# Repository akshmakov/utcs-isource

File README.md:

# utcs-isource

Current Source Module (Schematic and PCB) for micro Transcranial Current Stimulalation (**utCS**)

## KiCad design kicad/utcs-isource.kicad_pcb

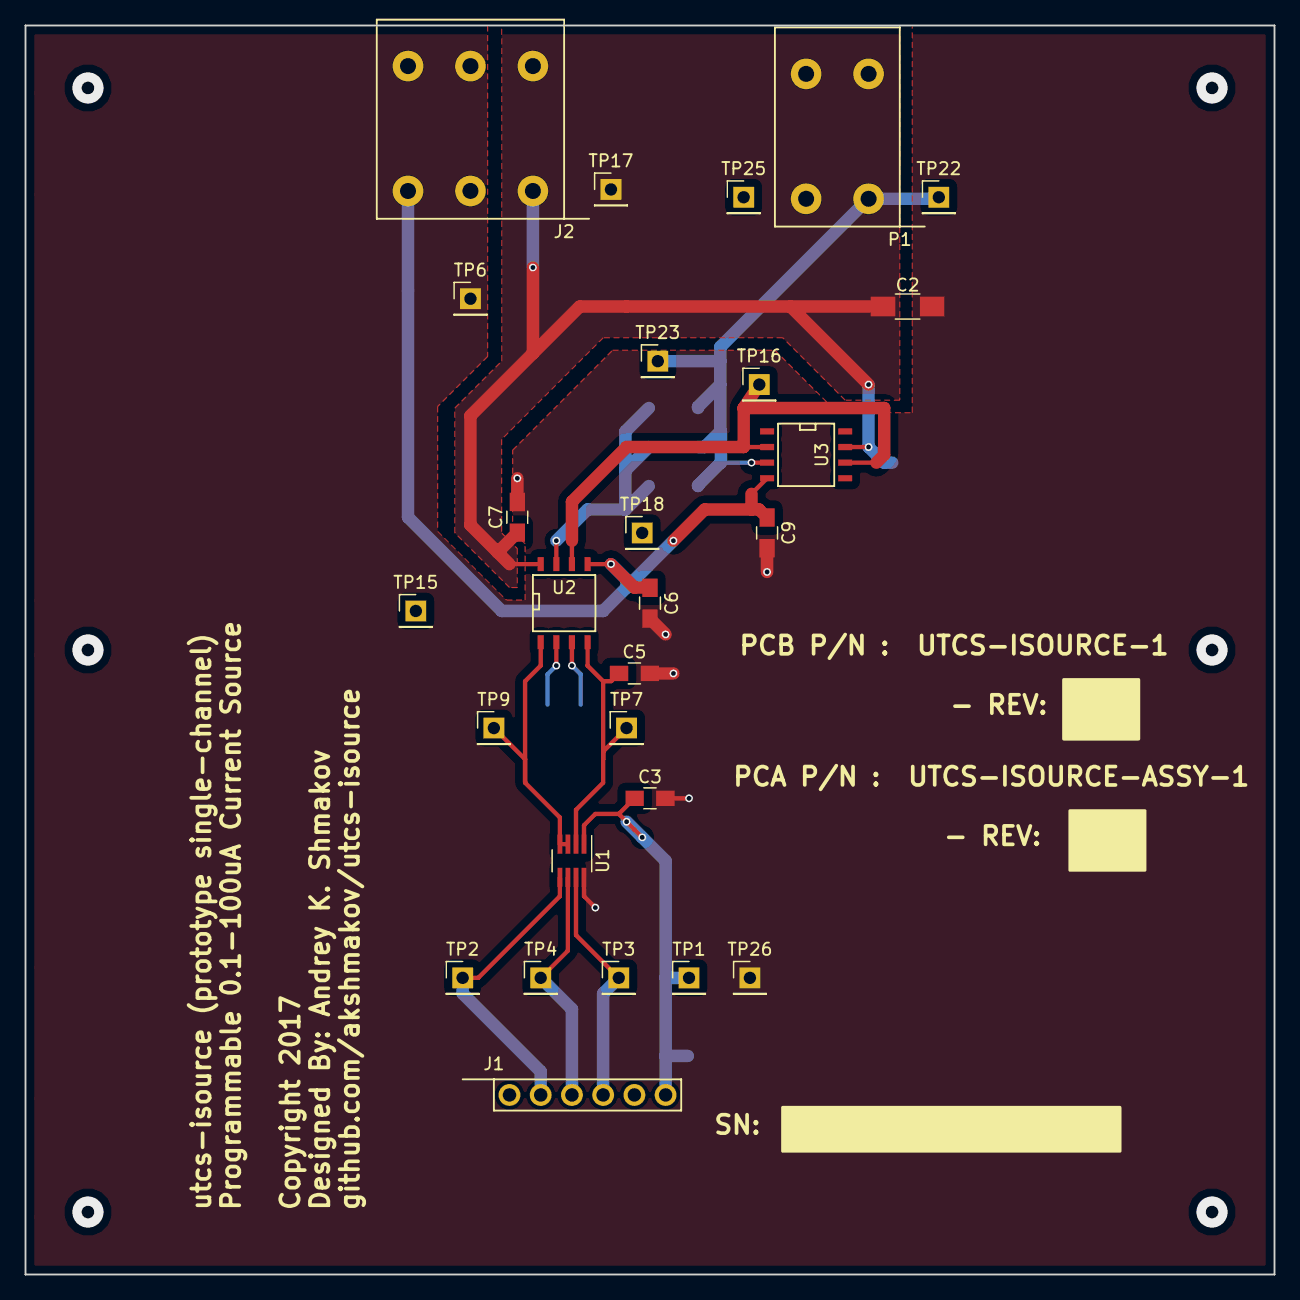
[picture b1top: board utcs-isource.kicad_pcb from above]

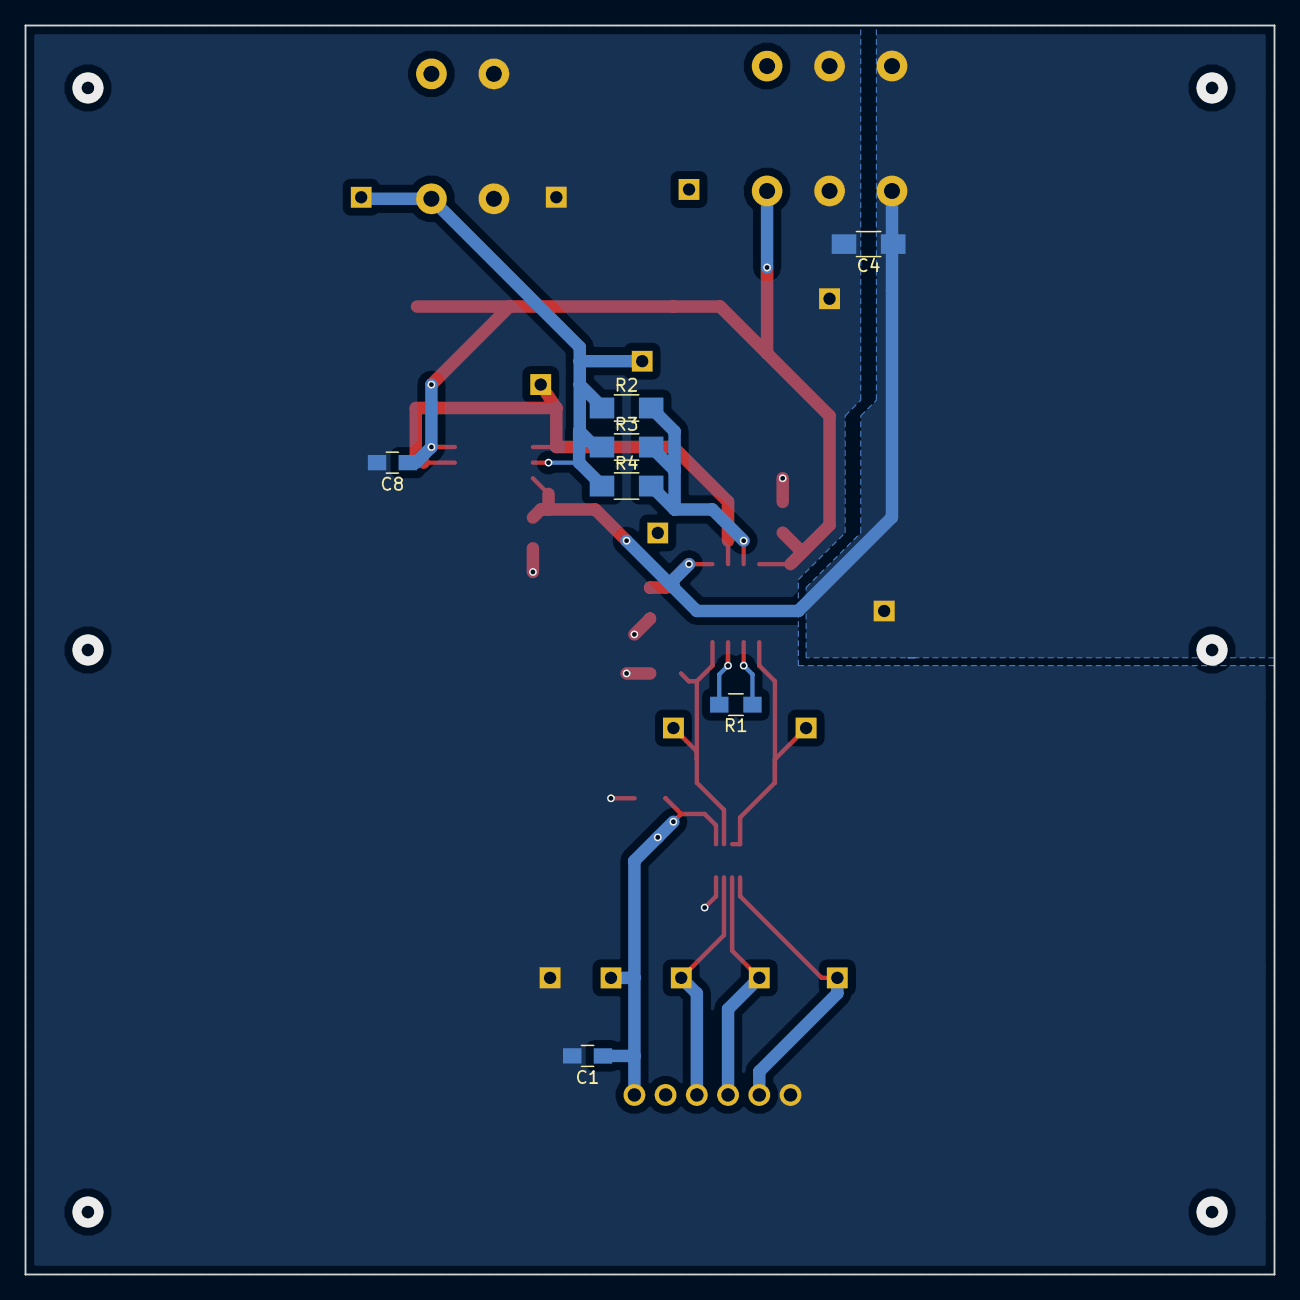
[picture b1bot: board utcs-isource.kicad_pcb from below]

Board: 2 copper layers, 101.6 x 101.6 mm, 34 parts (7 on the bottom side), 14 nets.

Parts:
C1: 100u; C_0805_HandSoldering
C2, C4: 100u; C_1206_HandSoldering
C3, C6, C7, C8, C9: 100n; C_0805_HandSoldering
C5: 10n; C_0805_HandSoldering
J1: Conn_01x06; PCB_HDR_100MIL_1X6_MOL-0705530005
J2: Conn_01x03; PCB_TB_1X3_PHC-1790296
P1: CONN_2; PCB_TB_1X2_PHC-1790283
R1: NP; R_0805_HandSoldering
R2: 1M; R_1206_HandSoldering
R3: 100K; R_1206_HandSoldering
R4: 10K; R_1206_HandSoldering
TP1: +5V; Pin_Header_Straight_1x01_Pitch2.54mm
TP2: ~CS; Pin_Header_Straight_1x01_Pitch2.54mm
TP3: MOSI; Pin_Header_Straight_1x01_Pitch2.54mm
TP4: SCLK; Pin_Header_Straight_1x01_Pitch2.54mm
TP6: AGND; Pin_Header_Straight_1x01_Pitch2.54mm
TP7: DAC_REF; Pin_Header_Straight_1x01_Pitch2.54mm
TP9: DAC_OUT; Pin_Header_Straight_1x01_Pitch2.54mm
TP15: AVSS; Pin_Header_Straight_1x01_Pitch2.54mm
TP16: INST_REF; Pin_Header_Straight_1x01_Pitch2.54mm
TP17: AVDD; Pin_Header_Straight_1x01_Pitch2.54mm
TP18: INSTR_OUT; Pin_Header_Straight_1x01_Pitch2.54mm
TP22, TP23: IOUT; Pin_Header_Straight_1x01_Pitch2.54mm
TP25: IRET; Pin_Header_Straight_1x01_Pitch2.54mm
TP26: GND; Pin_Header_Straight_1x01_Pitch2.54mm
U1: AD5660; SOT-23-8_Handsoldering
U2: AD8221; SOIC-8-N
U3: OP1177; SOIC-8-N

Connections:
+5V: C1.1, C3.1, J1.6, TP1.1, U1.1
/IOUT: P1.1, R2.1, R3.1, R4.1, TP22.1, TP23.1, U3.3
/SPI_MOSI: J1.4, TP3.1, U1.7
AVDD: C2.1, C7.1, C8.1, J2.1, TP17.1, U2.8, U3.7
AVSS: C4.1, C6.1, C9.1, J2.3, TP15.1, U2.5, U3.4
GND: C1.2, C2.2, C3.2, C4.2, C5.2, C6.2, C7.2, C8.2, C9.2, J1.1, J2.2, P1.2, TP6.1, TP25.1, TP26.1, U1.8
unnamed: C5.1, TP7.1, U1.2, U2.4
unnamed: J1.2, TP2.1, U1.5
unnamed: J1.3, TP4.1, U1.6
unnamed: R1.1, U2.2
unnamed: R1.2, U2.3
unnamed: R2.2, R3.2, R4.2, TP18.1, U2.7
unnamed: TP9.1, U1.3, U1.4, U2.1
unnamed: TP16.1, U2.6, U3.2, U3.6

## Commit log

2017-12-27 Place and Route Complete, finishing touches
2017-12-27 Initial P1 Fab
2017-12-28 Updated to double sided plating for through hole components
2017-12-28 First Pass re-org
2017-12-28 moved libraries to common position + hierarchical sheet test

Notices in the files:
kicad/utcs-isource.kicad_pcb:
Copyright 2017
